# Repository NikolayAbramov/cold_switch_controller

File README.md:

# Cold switch controller
This is the specialized polarized relay controller intended to drive an RF switches, installed inside a cryostat. It's mainly
affordable for switches similar to famous Radial products: https://www.radiall.com/products/rf-microwave-switches.html. Such switches are commonly used in experiments with superconducting RF devices, and, particularly, with quantum circuits. 

The first problem with such switches at the liquid He temperature 4K and below is that the resistance of their coils drops by ~100 times compared to room temperature values and it's no longer possible to drive them with a nominal voltage. The second is that the heat dissipation during switching must be controlled to ensure normal cryostat operation. I't especially important in case of dilution refrigerators, commonly used for experiments with quantum devices. 

To overcome the above mentioned problems the controller uses an adjustable pulsed current source instead of a voltage source to drive the coils. Both the current and pulse duration can be adjusted to achieve a reliable switching and a minimal power dissipation. Due to it's flexibility, the controller can be used to control RF switches also at room temperature which makes it a useful tool to have in you lab for test and experiment automation.

It has a minimalistic formfactor of a 3U Eurorack module with absolutely no cotrols - everything is done using a web interface or an SCPI commands.

# Specs

 - Power: 12V, fully protected against overvoltage up to 30V and reversed polarity
 - Interface: Ethernet with web interface and SCPI commands
 - Output: 2 channels for polarized SPnT switches with number of positions n up to 6
 - Drive current: 10-600 mA
 - Drive pulse width: 1 - 700 ms
 - Switch coil voltage: 12 V for room temperature operation, any for cryogenic applications

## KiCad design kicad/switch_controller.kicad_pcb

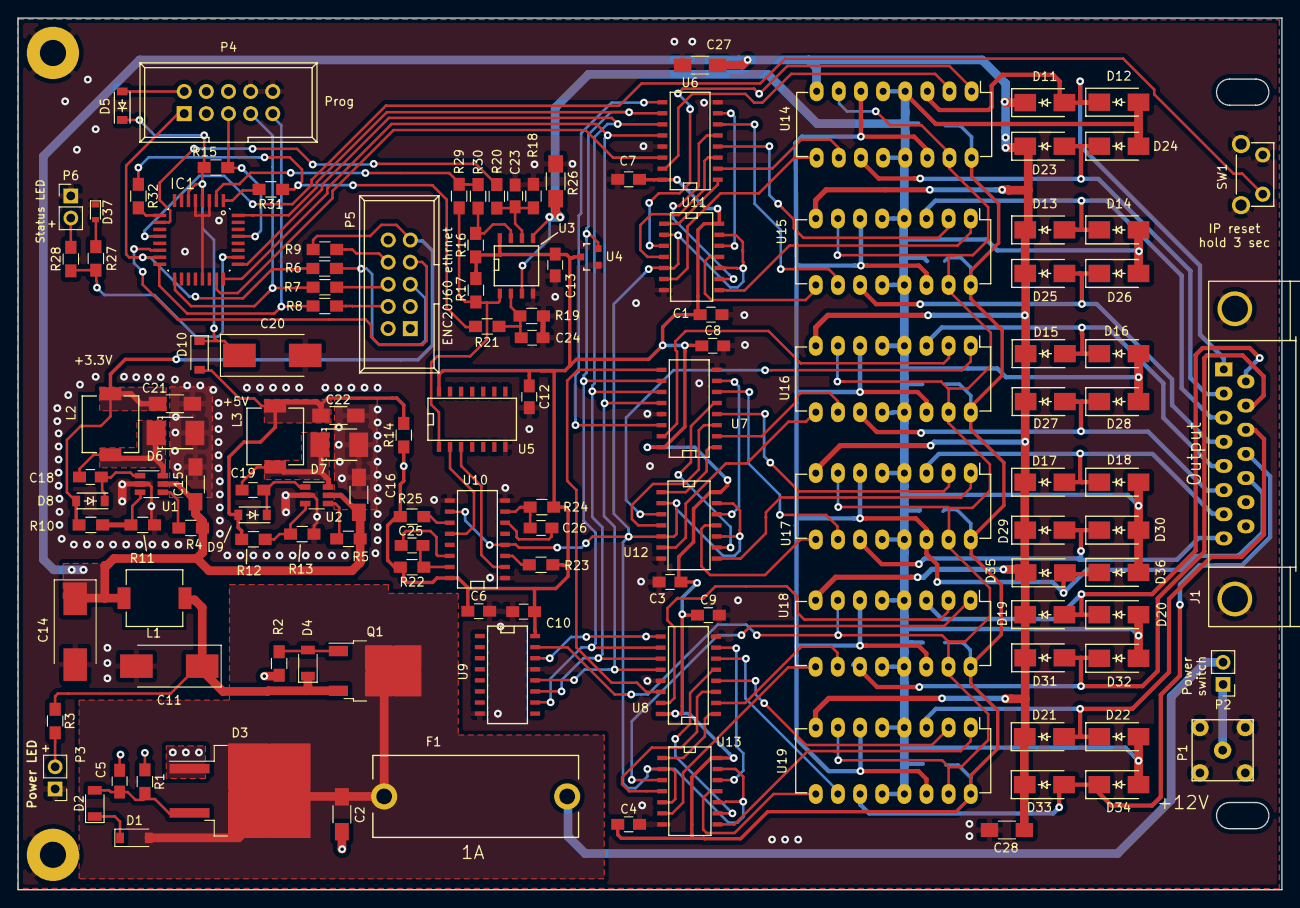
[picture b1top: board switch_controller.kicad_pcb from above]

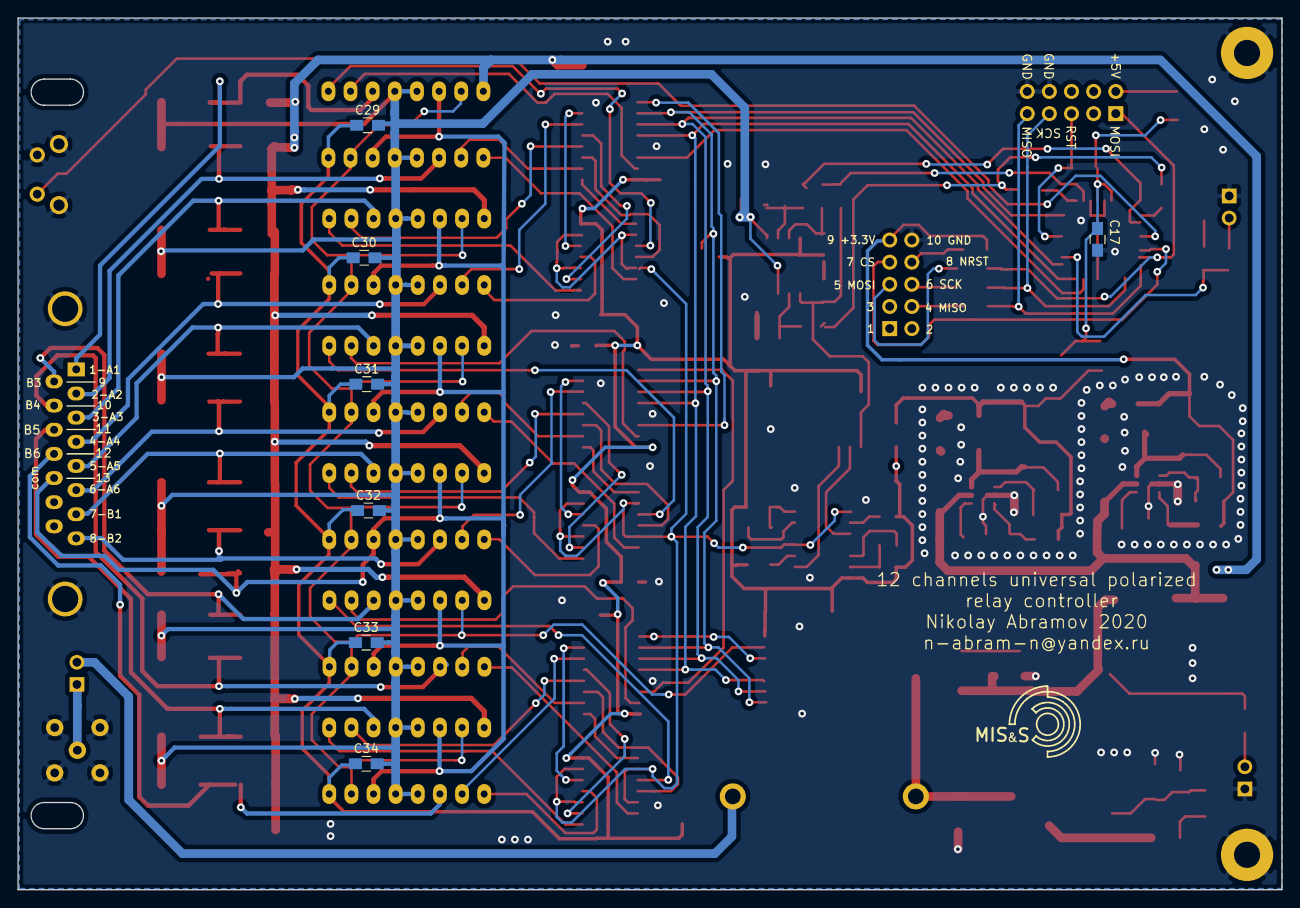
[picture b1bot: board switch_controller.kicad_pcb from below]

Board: 2 copper layers, 145.0 x 100.0 mm, 136 parts (7 on the bottom side), 112 nets.

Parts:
C1, C3, C4, C5, C6, C7, C8, C9, C10, C12, C13, C17, C29, C30, C31, C32, C33, C34: 0.1u; C_0805_HandSoldering
C2: 4.7u 50v; C_1206_HandSoldering
C11, C14: 100u; CP_Tantalum_Case-D_EIA-7343-31_Hand
C15, C16, C21, C22, C27, C28: 10u; C_1206_HandSoldering
C18, C19: 10n; C_0805_HandSoldering
C20: 100u 10v; CP_Tantalum_Case-D_EIA-7343-31_Hand
C23, C24: 4.7u; C_0805_HandSoldering
C25: 4n; C_0805_HandSoldering
C26: 2.2n; C_0805_HandSoldering
D1: PMEG6010CEH; D_SOD-123
D2, D4: BZV55-B15; D_1206
D3: VS-25TTS08S; TO-263-2
D5: MBR130LSFT1G; SOD-123
D6, D7: 10BQ030; DO-214AA
D8, D9: 1N4148; SOD-123
D10: MBR0520L; D_SOD-123
D11, D12, D13, D14, D15, D16, D17, D18, D19, D20, D21, D22, D23, D24, D25, D26, D27, D28, D29, D30, D31, D32, D33, D34, D35, D36: RS1A; DO-214BA_HandSoldering
D37: LED; D_0603
F1: Fuse; FH-101
IC1: ATMEGA328P-A; QFP_32
J1: DB15; DB15FR
L1, L2, L3: 33u; SRR0603
P1: LEMO; LEMO_00_R
P2: PWR_SWITCH; Pin_Header_Straight_1x02_Pitch2.54mm
P3: PWR_LED; Pin_Header_Straight_1x02_Pitch2.54mm
P4: PROG; IDC_Header_Straight_10pins
P5: ENC28J60; IDC_Header_Straight_10pins
P6: STATUS LED; Pin_Header_Straight_1x02_Pitch2.54mm
Q1: IRFR5305PBF; TO-252-2
R1, R3, R18, R27, R28: 1k; R_0805_HandSoldering
R2, R9, R15, R23, R25: 10k; R_0805_HandSoldering
R4, R5: 100k; R_0805_HandSoldering
R6, R7: 100; R_0805_HandSoldering
R8: 270; R_0805_HandSoldering
R10: 15k; R_0805_HandSoldering
R11: 4.7k; R_0805_HandSoldering
R12: 68k; R_0805_HandSoldering
R13: 13k; R_0805_HandSoldering
R14, R29, R30, R31, R32: 0; R_0805_HandSoldering
R16, R17: 3.3k; R_0805_HandSoldering
R19, R20, R21: 2k; R_0805_HandSoldering
R22, R24: 12k; R_0805_HandSoldering
R26: 2; R_1206_HandSoldering
SW1: IP_reset; SW_Tactile_SPST_Angled
U1, U2: LM2734; TSOT-23-6
U3: LM393; SOIC-8-N
U4: TMC809; SOT-23
U5, U11, U12, U13: 74LS08; SOIC-14_N
U6, U7, U8, U9: 74HC595; SO-16-N
U10: 74LS123; SO-16-N
U14, U15, U16, U17, U18, U19: L293B; DIP-16_W7.62mm_LongPads

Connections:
+3V3: C21.1, D8.2, L2.2, P5.9, R9.2, R10.1
+5V: C1.1, C3.1, C4.1, C6.1, C7.1, C8.1, C9.1, C10.1, C12.1, C13.1, C29.1, C30.1, C31.1, C32.1, C33.1, C34.1, R14.1, R16.2, R17.2, R22.2, R23.2, R24.1, R25.2, U3.8, U4.3, U5.14, U6.16, U7.16, U8.16, U9.16, U10.16, U11.14, U12.14, U13.14, U14.16, U15.16, U16.16, U17.16, U18.16, U19.16
+12V: C14.1, C15.1, C16.1, C27.1, C28.1, D11.1, D13.1, D15.1, D17.1, D19.1, D21.1, D23.1, D25.1, D27.1, D29.1, D31.1, D33.1, D35.1, L1.2, R4.2, R5.2, U1.5, U2.5, U14.8, U15.8, U16.8, U17.8, U18.8, U19.8
/+5VMCU: C17.1, C20.1, D5.1, D10.1, IC1.4, IC1.6, R15.1
/A1: U6.15, U14.2
/A1EN: U6.1, U11.1
/A1_out: D11.2, D12.1, J1.1, U14.3
/A2: U6.2, U14.10
/A2EN: U6.3, U11.4
/A2_out: D23.2, D24.1, J1.2, U14.11
/A3: U6.4, U15.2
/A3EN: U6.5, U11.9
/A3_out: D13.2, D14.1, J1.3, U15.3
/A4: U6.6, U15.10
/A4EN: U6.7, U11.12
/A4_out: D25.2, D26.1, J1.4, U15.11
/A5: U7.15, U16.2
/A5EN: U7.1, U12.1
/A5_out: D15.2, D16.1, J1.5, U16.3
/A6: U7.2, U16.10
/A6EN: U7.3, U12.4
/A6_out: D27.2, D28.1, J1.6, U16.11
/B1: U7.4, U17.2
/B1EN: U7.5, U12.9
/B1_out: D17.2, D18.1, J1.7, U17.3
/B2: U7.6, U17.10
/B2EN: U7.7, U12.12
/B2_out: D29.2, D30.1, J1.8, U17.11
/B3: U8.15, U18.2
/B3EN: U8.1, U13.1
/B3_out: D19.2, D20.1, J1.9, U18.3
/B4: U8.2, U18.10
/B4EN: U8.3, U13.4
/B4_out: D31.2, D32.1, J1.10, U18.11
/B5: U8.4, U19.2
/B5EN: U8.5, U13.9
/B5_out: D21.2, D22.1, J1.11, U19.3
/B6: U8.6, U19.10
/B6EN: U8.7, U13.12
/B6_out: D33.2, D34.1, J1.12, U19.11
/CS: IC1.14, P5.7
/Com: U9.15, U14.7, U14.15, U15.7, U15.15, U16.7, U16.15, U17.7, U17.15, U18.7, U18.15, U19.7, U19.15
/Com_out: D35.2, D36.1, J1.13, U14.6, U14.14, U15.6, U15.14, U16.6, U16.14, U17.6, U17.14, U18.6, U18.14, U19.6, U19.14
/I_fb: IC1.2, R29.1, R30.1
/Iref: R21.2, R31.1, R32.1
/Isens: IC1.10, R20.1
/LC: IC1.24, U6.12, U7.12, U8.12, U9.12
/LED: IC1.26, R27.1, R28.1
/LowVCC: IC1.32, U4.2, U6.10, U7.10, U8.10, U9.10
/MISO: IC1.16, P4.9, R8.2
/MOSI: IC1.15, P4.1, R6.1
/RST: IC1.29, P4.5, R15.2
/SC: IC1.25, U6.11, U7.11, U8.11, U9.11
/SCK: IC1.17, P4.7, R7.1
/SDI: IC1.23, U6.14
GND: C1.2, C2.2, C3.2, C4.2, C5.2, C6.2, C7.2, C8.2, C9.2, C10.2, C11.2, C12.2, C13.2, C14.2, C15.2, C16.2, C17.2, C20.2, C21.2, C22.2, C23.1, C24.1, C27.2, C28.2, D3.1, D6.2, D7.2, D37.1, IC1.3, IC1.5, IC1.21, P1.2, P3.1, P4.8, P4.10, P5.10, P6.1, R1.1, R2.1, R11.2, R13.2, R18.2, R19.2, R26.2, SW1.1, U1.2, U2.2, U3.4, U4.1, U5.7, U6.8, U6.13, U7.8, U7.13, U8.8, U8.13, U9.8, U9.13, U10.1, U10.8, U10.9, U11.7, U12.7, U13.7
unnamed: C2.1, D1.2, D3.2, F1.1, Q1.2
unnamed: C5.1, D2.2, D3.3, R1.2
unnamed: C11.1, D4.1, L1.1, Q1.3, R3.1
unnamed: C18.1, D8.1, U1.1
unnamed: C18.2, D6.1, L2.1, U1.6
unnamed: C19.1, D9.1, U2.1
unnamed: C19.2, D7.1, L3.1, U2.6
unnamed: C22.1, D9.2, D10.2, L3.2, R12.1, R14.2
unnamed: C23.2, R18.1, R20.2, U3.6
unnamed: C24.2, R19.1, R21.1, U3.2
unnamed: C25.1, U10.14
unnamed: C25.2, R22.1, U10.15
unnamed: C26.1, U10.6
unnamed: C26.2, R24.2, U10.7
unnamed: C29.2, C30.2, C31.2, C32.2, C33.2, C34.2, D12.2, D14.2, D16.2, D18.2, D20.2, D22.2, D24.2, D26.2, D28.2, D30.2, D32.2, D34.2, D36.2, R26.1, U3.3, U3.5, U14.4, U14.5, U14.12, U14.13, U15.4, U15.5, U15.12, U15.13, U16.4, U16.5, U16.12, U16.13, U17.4, U17.5, U17.12, U17.13, U18.4, U18.5, U18.12, U18.13, U19.4, U19.5, U19.12, U19.13
unnamed: D1.1, D2.1
unnamed: D4.2, Q1.1, R2.2
unnamed: D5.2, P4.2
unnamed: D37.2, R27.2
unnamed: F1.2, P2.2
unnamed: IC1.1, R31.2
unnamed: IC1.9, R32.2
unnamed: IC1.12, SW1.2
unnamed: P1.1, P2.1
unnamed: P3.2, R3.2
unnamed: P5.4, R8.1
unnamed: P5.5, R6.2
unnamed: P5.6, R7.2
unnamed: P5.8, R9.1
unnamed: P6.2, R28.2
unnamed: R4.1, U1.4
unnamed: R5.1, U2.4
unnamed: R10.2, R11.1, U1.3
unnamed: R12.2, R13.1, U2.3
unnamed: R16.1, R30.2, U3.7
unnamed: R17.1, R29.2, U3.1, U5.1
unnamed: R23.1, U10.3
unnamed: R25.1, U10.11
unnamed: U6.9, U7.14
unnamed: U7.9, U8.14
unnamed: U8.9, U9.14
unnamed: U5.3, U10.2
unnamed: U10.4, U10.10, U11.2, U11.5, U11.10, U11.13, U12.2, U12.5, U12.10, U12.13, U13.2, U13.5, U13.10, U13.13
unnamed: U5.2, U10.12
unnamed: U11.3, U14.1
unnamed: U11.6, U14.9
unnamed: U11.8, U15.1
unnamed: U11.11, U15.9
unnamed: U12.3, U16.1
unnamed: U12.6, U16.9
unnamed: U12.8, U17.1
unnamed: U12.11, U17.9
unnamed: U13.3, U18.1
unnamed: U13.6, U18.9
unnamed: U13.8, U19.1
unnamed: U13.11, U19.9

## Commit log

2022-12-10 new file: EuroBox_rear_panel/switch_controller_rear.PDF new file: EuroBox_rear_panel/switch_controller_rear.SLDDRW new file: EuroBox_rear_panel/switch_controller_rear.SLDPRT new file: firmware/.gitig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
2022-12-10 new file: README.md
2022-12-11 PDF schematics added
2023-09-29 Watchdog added
2023-09-29 modified: firmware/src/Release/cold_sw_drv.hex modified: firmware/src/main.c modified: kicad/switch_controller.kicad_prl modified: kicad/switch_controller.kicad_pro kicad/_autosave-switch_controller.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
2023-09-29 modified: kicad/.gitignore new file: kicad/switch_controller.kicad_sch
2023-09-30 kicad .gitignore update
2023-10-02 ENC28J60 state monitoring added
